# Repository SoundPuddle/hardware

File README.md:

hardware
========

Hardware designs for the SoundPuddle project

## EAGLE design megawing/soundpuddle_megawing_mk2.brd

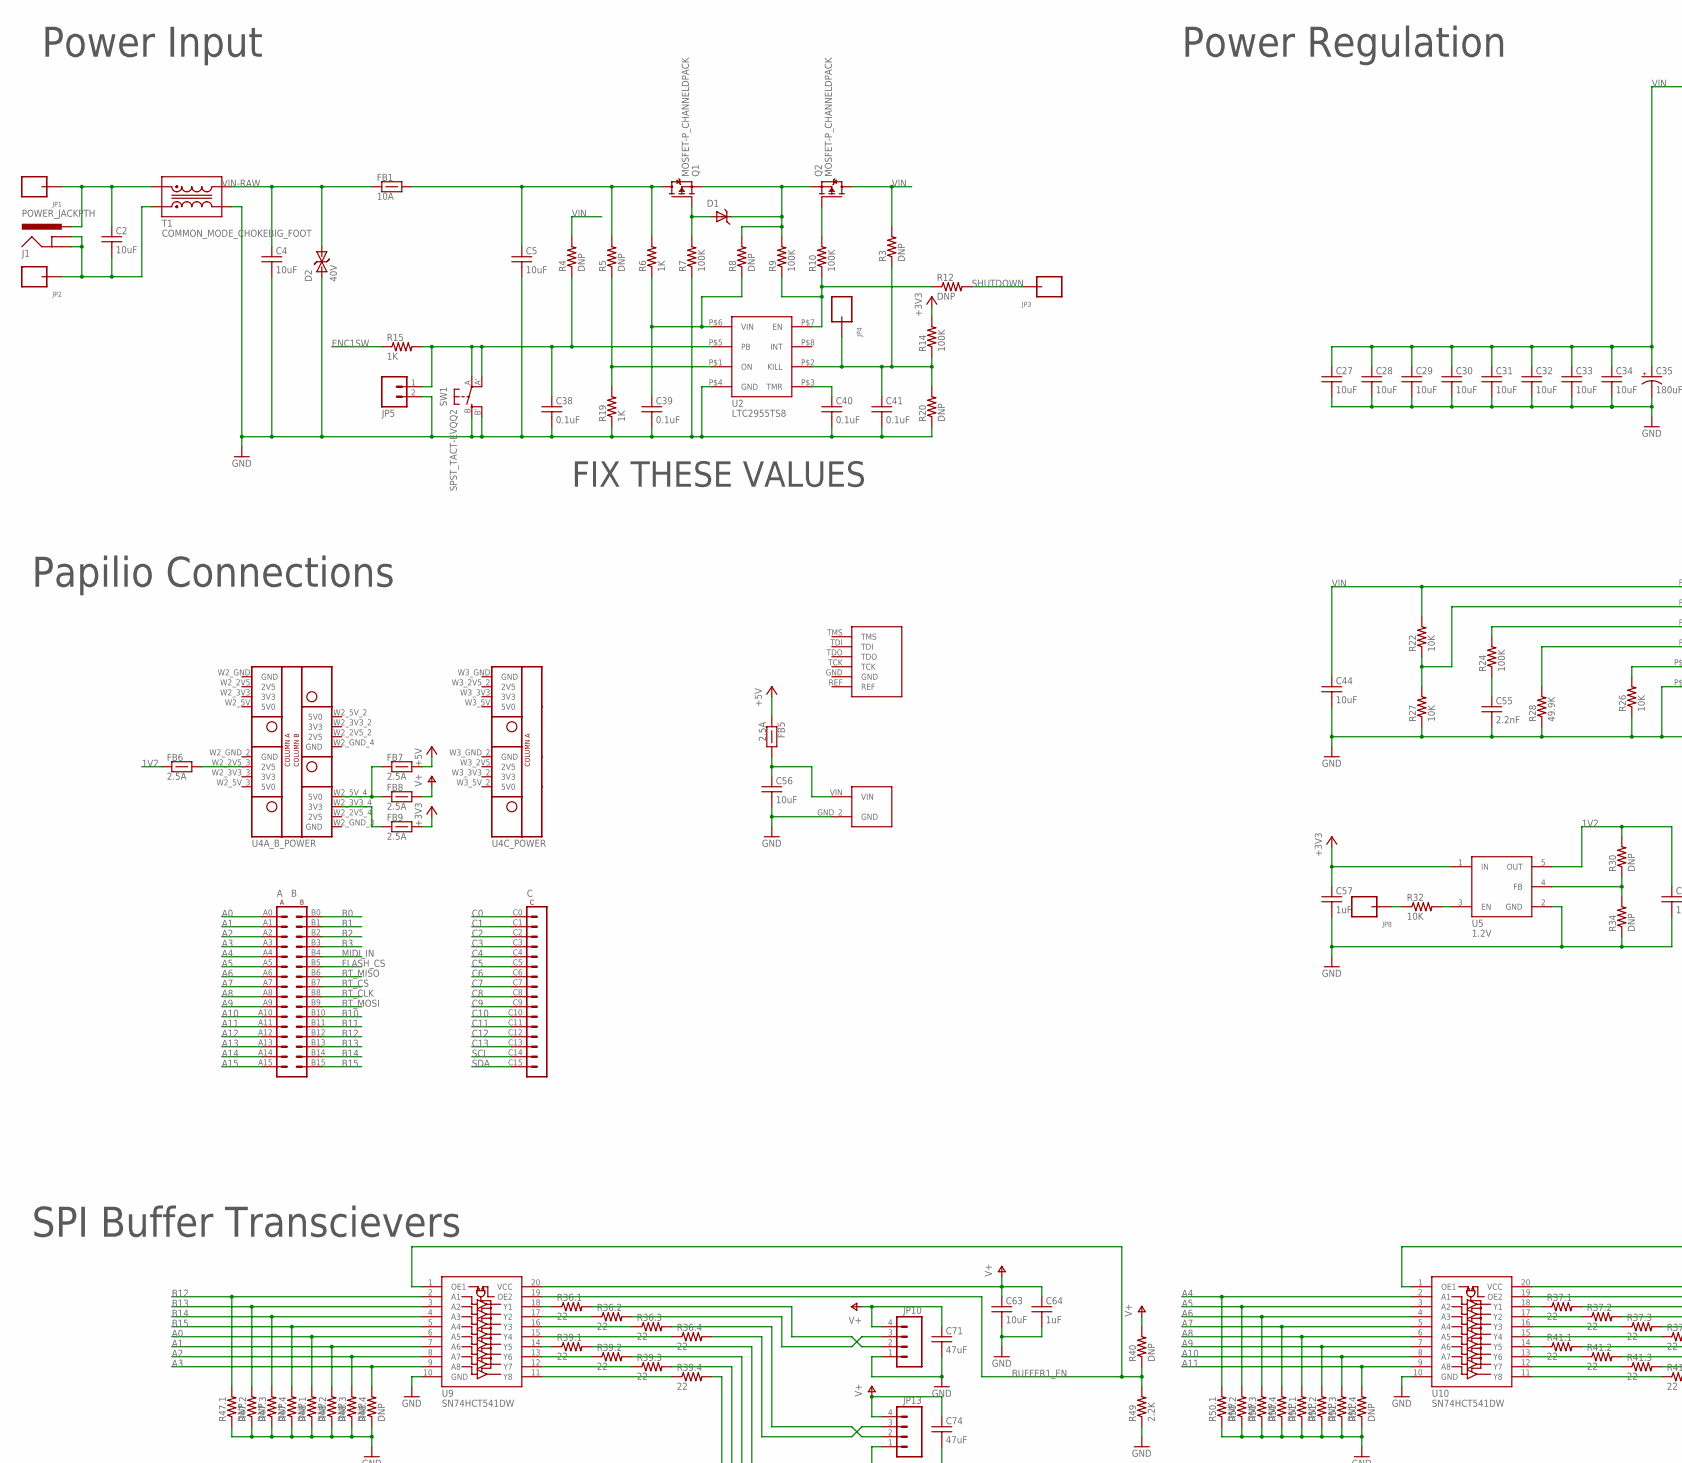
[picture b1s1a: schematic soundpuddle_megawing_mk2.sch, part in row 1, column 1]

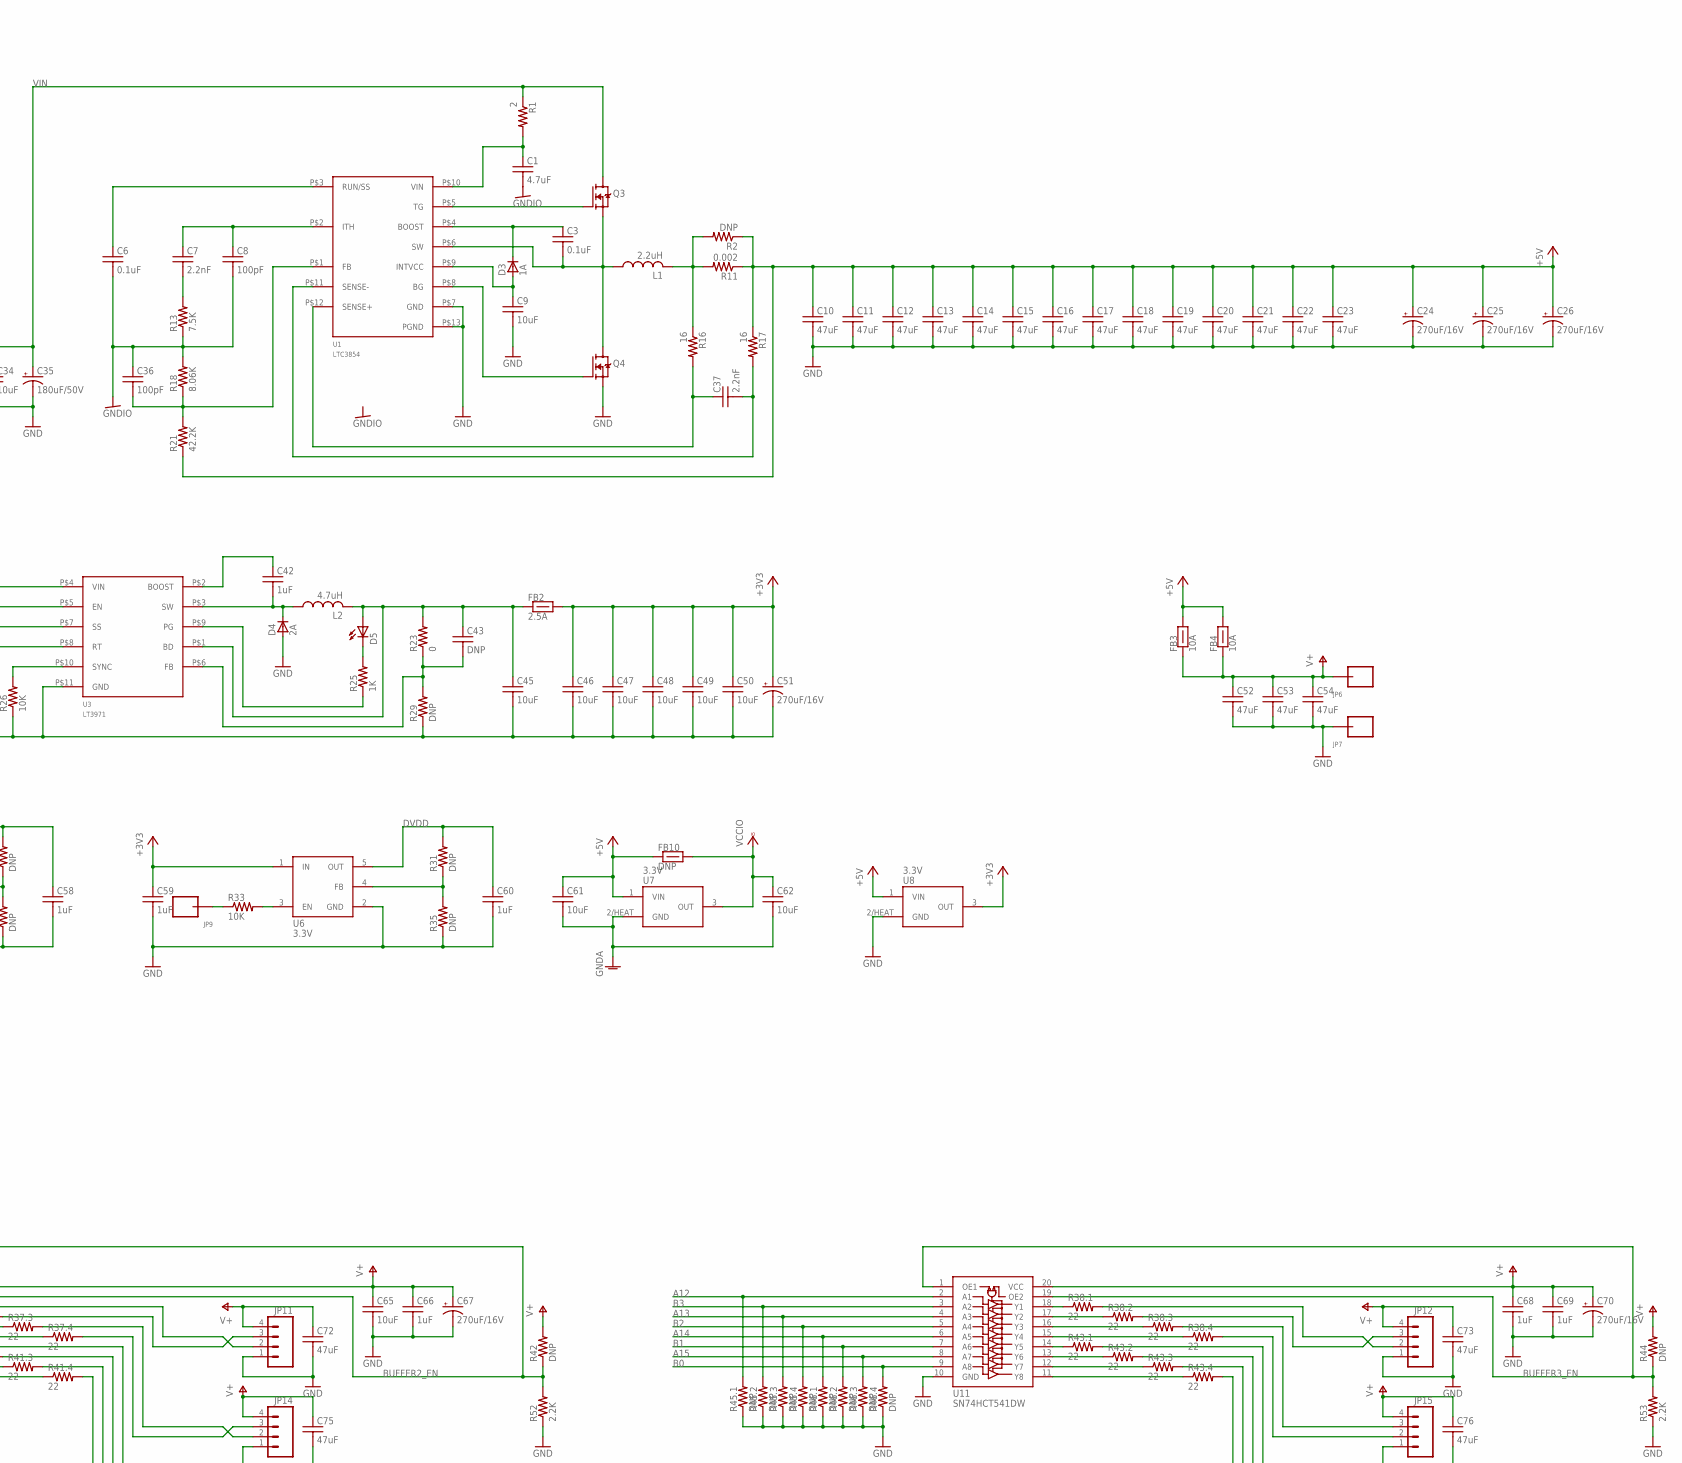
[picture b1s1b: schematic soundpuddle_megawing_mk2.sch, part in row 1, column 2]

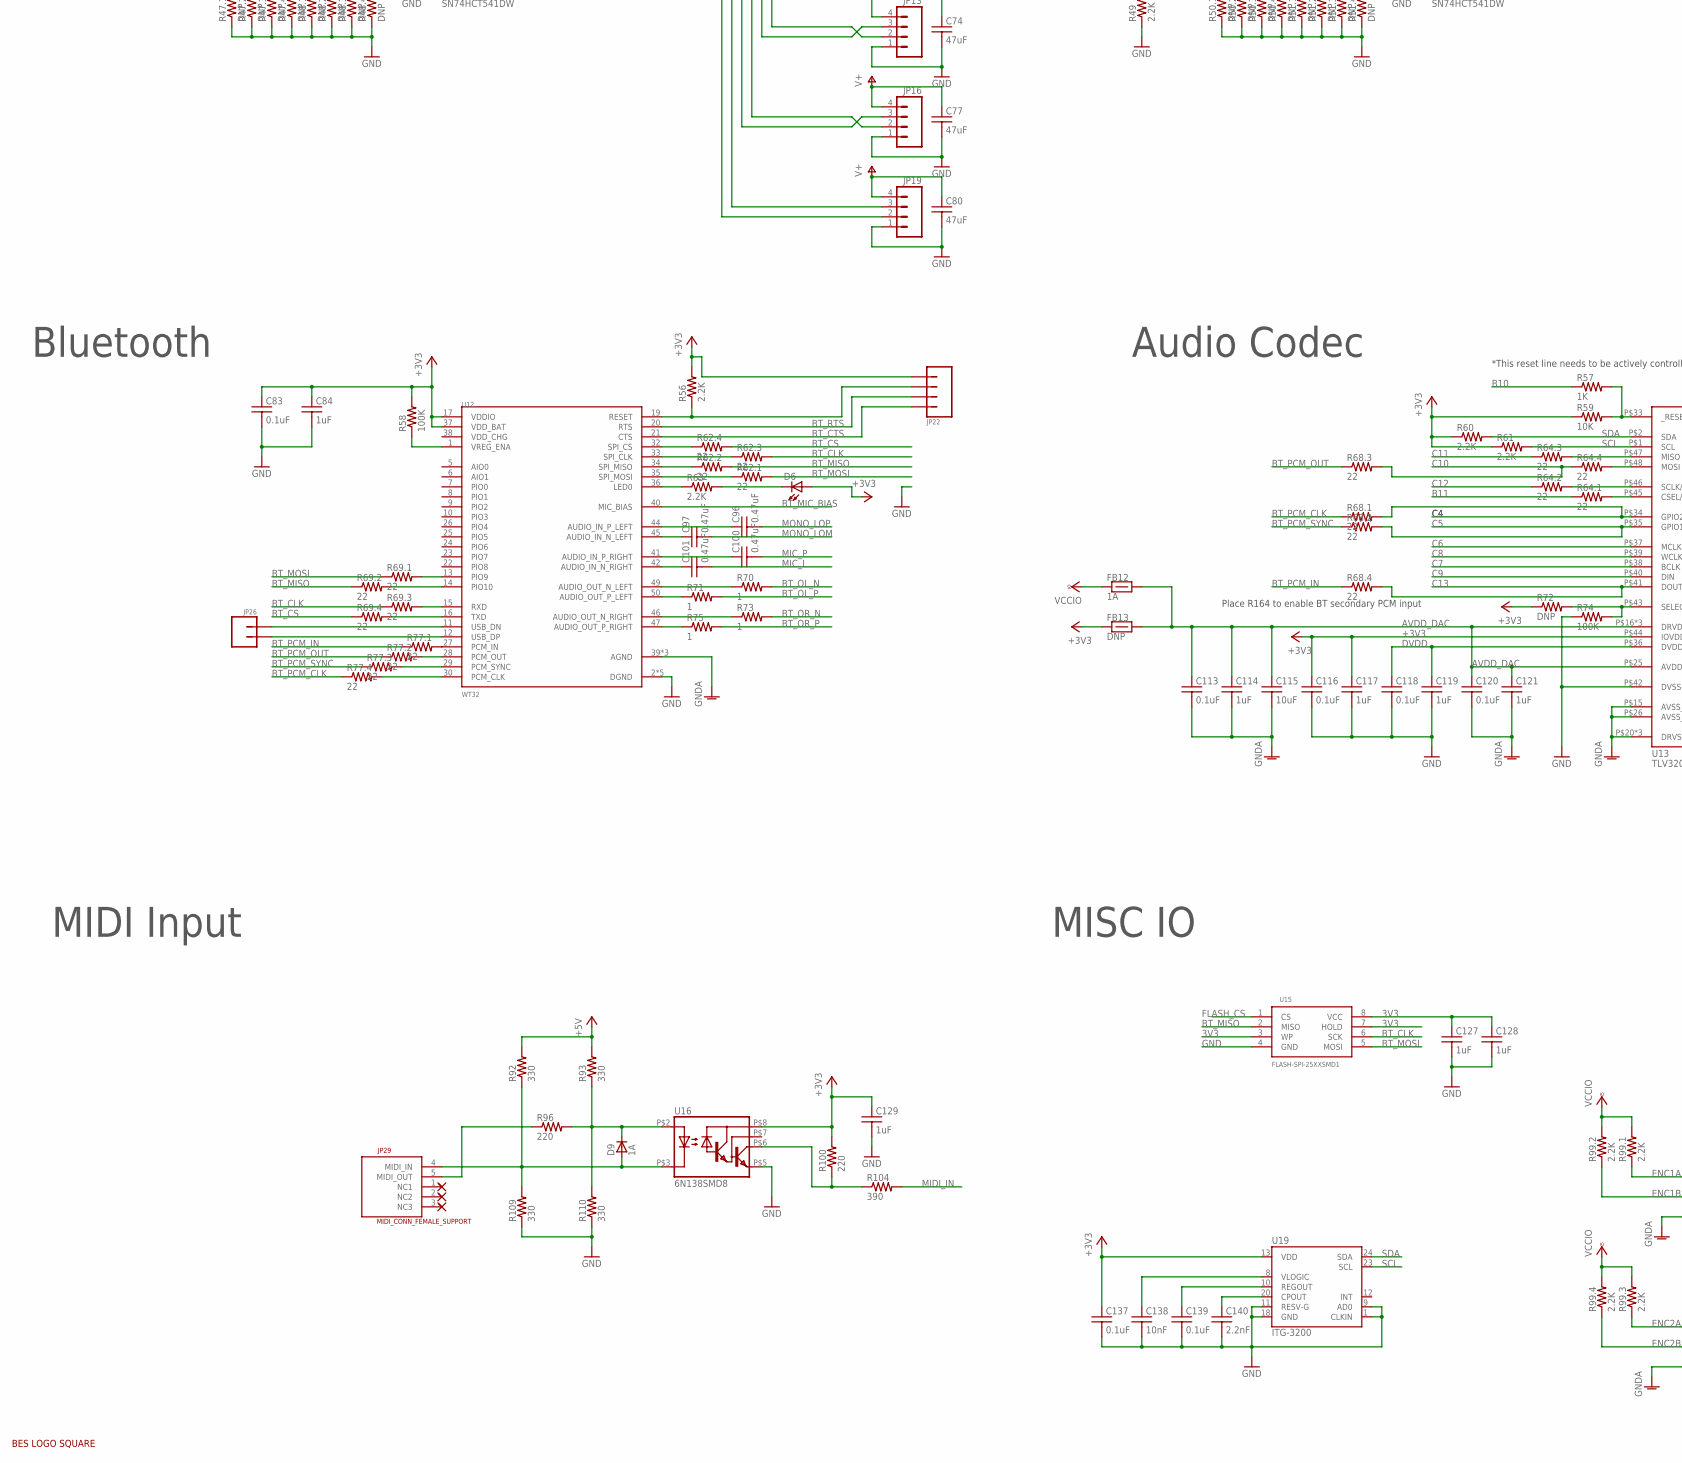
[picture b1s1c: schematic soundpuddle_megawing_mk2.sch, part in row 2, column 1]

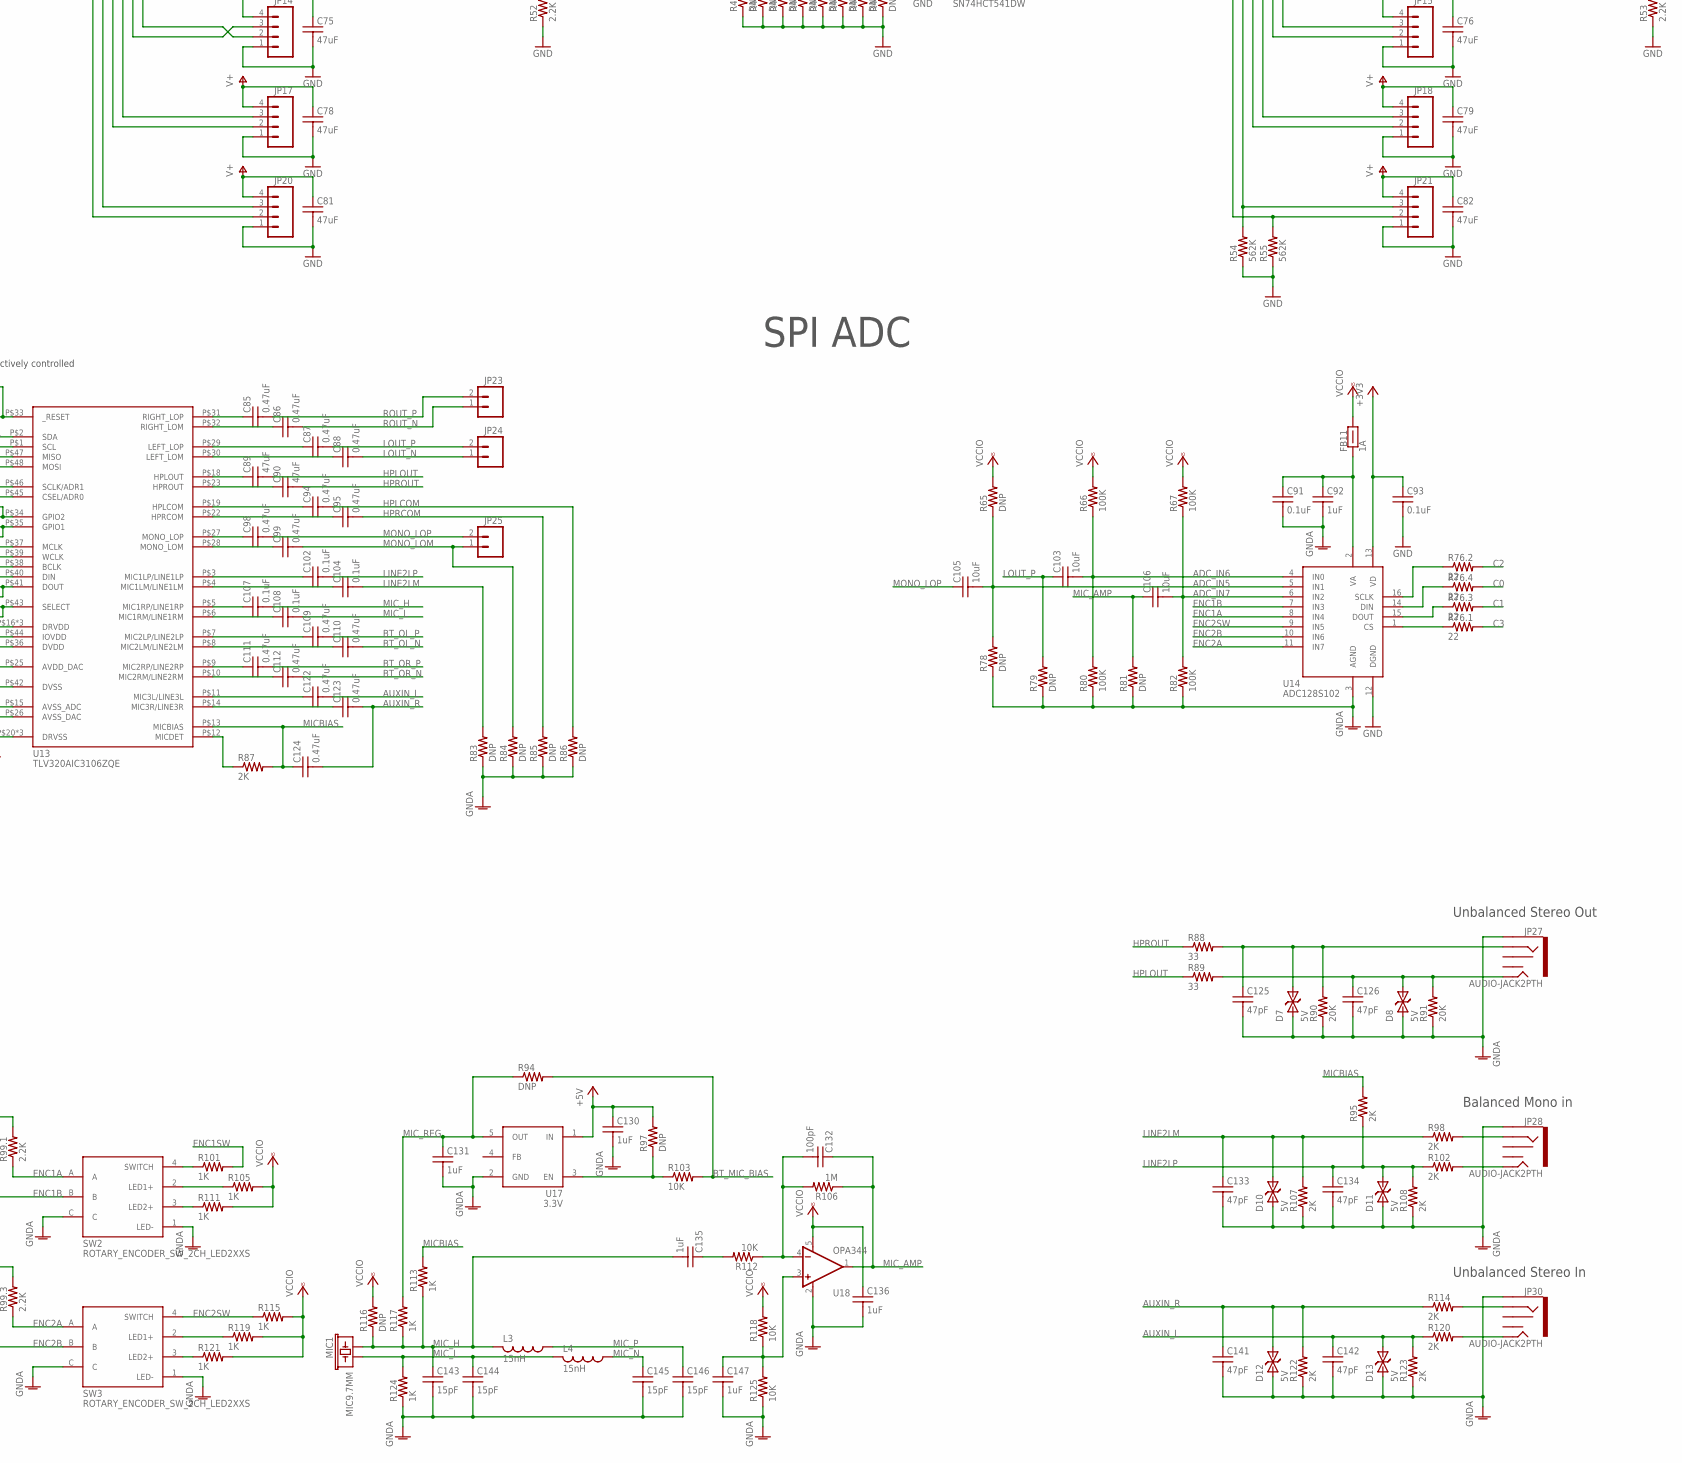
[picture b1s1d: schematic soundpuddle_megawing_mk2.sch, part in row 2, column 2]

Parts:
C1: 4.7uF; 0603
C2, C4, C5, C27, C28, C29, C30, C31, C32, C33, C34, C44, C45, C46, C47, C48, C49, C50, C56, C61, C62: 10uF; 1206
C3, C102, C104: 0.1uF; 0805
C6, C38, C39, C40, C41, C83, C91, C93, C107, C108, C113, C116, C118, C120, C137, C139: 0.1uF; 0603
C7, C37, C55, C140: 2.2nF; 0603
C8, C36, C132: 100pF; 0603
C9, C103, C105, C106, C115: 10uF; 0805
C10, C11, C12, C13, C14, C15, C16, C17, C18, C19, C20, C21, C22, C23, C52, C53, C54, C71, C72, C73, C74, C75, C76, C77, C78, C79, C80, C81, C82, C89, C90: 47uF; 1206
C24, C25, C26, C51, C67, C70: 270uF/16V; CAP_RADIAL_THRUHOLE_8MM_DIA
C35: 180uF/50V; CAP_RADIAL_THRUHOLE_8MM_DIA
C42, C57, C58, C59, C60, C64, C66, C68, C69, C84, C92, C114, C117, C119, C121, C127, C128, C129, C130, C131, C135, C136, C147: 1uF; 0603
C43: DNP; 0603
C63, C65: 10uF; 0603
C85, C86, C87, C88, C94, C95, C96, C97, C98, C99, C100, C101, C109, C110, C111, C112, C122, C123, C124: 0.47uF; 0805
C125, C126, C133, C134, C141, C142: 47pF; 0603
C138: 10nF; 0603
C143, C144, C145, C146: 15pF; 0603
D1: ZENER_SOD-323; SOD-323
D2: 40V; SMB
D3, D9: 1A; SOD-123F
D4: 2A; DIODE_DO-214AC
D5, D6: LED0805; LED_0805
D7, D8, D10, D11, D12, D13: 5V; 0603
FB1, FB3, FB4: 10A; 1612
FB2, FB5, FB6, FB7, FB8, FB9: 2.5A; 0805
FB10, FB13: DNP; 0603
FB11, FB12: 1A; 0603
J1: POWER_JACKPTH; POWER_JACK_PTH
JP1, JP2, JP6, JP7: ANDERSON_POWERPOLEVERTICAL; ANDERSON_25A_VERTICAL_1P
JP3, JP4, JP8, JP9: HEADER-SMALL-1PIN; HEADER-SMALL-1PIN-0.036IN
JP5: M02PTH; 1X02
JP10, JP11, JP12, JP13, JP14, JP15, JP16, JP17, JP18, JP19, JP20, JP21: M04POLAR; MOLEX-1X4
JP22: HEADER-SMALL-4PIN0.1IN; HEADER-SMALL-4PIN-0.036IN
JP23, JP24, JP25: M02POLAR; MOLEX-1X2
JP26: HEADER-SMALL-2PIN0.1IN; HEADER-SMALL-2PIN-0.036IN
JP27, JP28, JP30: AUDIO-JACK2PTH; AUDIO-JACK
JP29: MIDI_CONN_FEMALE_SUPPORT; DIN_5_FEMALE_SUPPORT
L1: 2.2uH; INDUCTOR_HC1
L2: 4.7uH; INDUCTOR_6X6MM
L3, L4: 15nH; 0805
LOGO: LOGO
MIC1: MIC9.7MM; MIC-9.7MM
Q1, Q2: MOSFET-P_CHANNELDPACK; DPACK_1
Q3, Q4: MOSFET_N_CHANNELLFPAK; POWERPAK_SO-8_LFPAK
R1: 2; 0603
R2: DNP; 2512
R3, R4, R5, R8, R12, R20, R29, R30, R31, R34, R35, R40, R42, R44, R65, R72, R78, R79, R81, R83, R84, R85, R86, R94, R97, R116: DNP; 0603
R6, R15, R19, R25, R57, R101, R105, R111, R113, R115, R117, R119, R121, R124: 1K; 0603
R7, R9, R10, R14, R24, R58, R66, R67, R74, R80, R82: 100K; 0603
R11: 0.002; 2512
R13: 7.5K; 0603
R16, R17: 16; 0805
R18: 8.06K; 0603
R21: 42.2K; 0603
R22, R26, R27, R32, R33, R59, R103, R112, R118, R125: 10K; 0603
R23: 0; 0603
R28: 49.9K; 0603
R36, R37, R38, R39, R41, R43, R62, R64, R68, R69, R76, R77: 22; RESISTOR_ARRAY_1206_4CH_CRA06S
R45, R46, R47, R48, R50, R51: DNP; RESISTOR_ARRAY_1206_4CH_CRA06S
R49, R52, R53, R56, R60, R61, R63: 2.2K; 0603
R54, R55: 562K; 0603
R70, R71, R73, R75: 1; 0805
R87, R95, R107, R108, R122, R123: 2K; 0603
R88, R89: 33; 0805
R90, R91: 20K; 0603
R92, R93, R109, R110: 330; 0603
R96, R100: 220; 0603
R98, R102, R114, R120: 2K; 0805
R99: 2.2K; RESISTOR_ARRAY_1206_4CH_CRA06S
R104: 390; 0603
R106: 1M; 0603
SW1: SPST_TACT-EVQQ2; EVQ-Q2
SW2, SW3: ROTARY_ENCODER_SW_2CH_LED2XXS; ROTARY_ENCODER_BOURNS_PEL12D
T1: COMMON_MODE_CHOKEBIG_FOOT; CM-CHOKE_PULSE_BIG-FOOT
U1: LTC3854; MSOP12+1
U2: LTC2955TS8; TSOT-23-8
U3: LT3971; MSOP10+1_LT
U4: PAPILIO_PLUS_MEGAWING; PAPILIO_PLUS
U5: 1.2V; TSOT23
U6, U17: 3.3V; TSOT23
U7, U8: 3.3V; DPACK_1
U9, U10, U11: SN74HCT541DW; SOIC-20_TI_DW
U12: WT32; WT32_BT_MODULE
U13: TLV320AIC3106ZQE; QFN48+1
U14: ADC128S102; TSSOP16
U15: FLASH-SPI-25XXSMD1; SO08-EIAJ
U16: 6N138SMD8; SMD-8
U18: OPA344; SOT23-5
U19: ITG-3200; QFN-24

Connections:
1V2: C58.1, FB6.1, R30.2, U5.5 (OUT)
3V3: C127.1, C128.1, U15.3 (WP), U15.7 (HOLD), U15.8 (VCC)
+3V3: C46.P$1 (1), C47.P$1 (1), C48.P$1 (1), C49.P$1 (1), C50.P$1 (1), C51.P$2 (+), C57.1, C59.1, C83.1, C84.1, C93.1, C116.1, C117.1, C129.1, C137.1, D6.1 (A), FB2.2, FB9.2, FB13.1, JP22.P$4, R14.2, R56.2, R58.2, R59.1, R60.1, R61.1, R72.1, R100.2, U5.1 (IN), U6.1 (IN), U8.3 (OUT), U12.17 (VDDIO), U12.37 (VDD_BAT), U13.P$44 (IOVDD), U14.13 (VD), U16.P$8 (VCC), U19.13 (VDD)
+5V: C10.P$1 (1), C11.P$1 (1), C12.P$1 (1), C13.P$1 (1), C14.P$1 (1), C15.P$1 (1), C16.P$1 (1), C17.P$1 (1), C18.P$1 (1), C19.P$1 (1), C20.P$1 (1), C21.P$1 (1), C22.P$1 (1), C23.P$1 (1), C24.P$2 (+), C25.P$2 (+), C26.P$2 (+), C61.P$1 (1), C130.1, FB3.2, FB4.2, FB5.1, FB7.2, FB10.1, R2.1, R11.1, R17.1, R21.1, R92.2, R93.2, R97.2, U7.1 (VIN), U8.1 (VIN), U17.1 (IN)
A0: R48.P$8 (2), U4.A0, U9.6 (A5)
A1: R48.P$7 (2), U4.A1, U9.7 (A6)
A2: R48.P$6 (2), U4.A2, U9.8 (A7)
A3: R48.P$5 (2), U4.A3, U9.9 (A8)
A4: R50.P$8 (2), U4.A4, U10.2 (A1)
A5: R50.P$7 (2), U4.A5, U10.3 (A2)
A6: R50.P$6 (2), U4.A6, U10.4 (A3)
A7: R50.P$5 (2), U4.A7, U10.5 (A4)
A8: R51.P$8 (2), U4.A8, U10.6 (A5)
A9: R51.P$7 (2), U4.A9, U10.7 (A6)
A10: R51.P$6 (2), U4.A10, U10.8 (A7)
A11: R51.P$5 (2), U4.A11, U10.9 (A8)
A12: R45.P$8 (2), U4.A12, U11.2 (A1)
A13: R45.P$6 (2), U4.A13, U11.4 (A3)
A14: R46.P$8 (2), U4.A14, U11.6 (A5)
A15: R46.P$6 (2), U4.A15, U11.8 (A7)
ADC_IN5: C105.2, R65.1, R78.2, U14.5 (IN1)
ADC_IN6: C103.2, R66.1, R80.2, U14.4 (IN0)
ADC_IN7: C106.2, R67.1, R82.2, U14.6 (IN2)
AUXIN_L: C122.2, C142.1, D13.1 (A), R120.1, R123.2
AUXIN_R: C123.2, C124.2, C141.1, D12.1 (A), R114.1, R122.2
AVDD_DAC: C113.1, C114.1, C115.1, C120.1, C121.1, FB12.2, FB13.2, U13.P$16 (DRVDD), U13.P$17 (DRVDD), U13.P$24 (DRVDD), U13.P$25 (AVDD_DAC)
B0: R46.P$5 (2), U4.B0, U11.9 (A8)
B1: R46.P$7 (2), U4.B1, U11.7 (A6)
B2: R45.P$5 (2), U4.B2, U11.5 (A4)
B3: R45.P$7 (2), U4.B3, U11.3 (A2)
B10: R57.1, U4.B10
B11: R64.P$1 (1), U4.B11
B12: R47.P$8 (2), U4.B12, U9.2 (A1)
B13: R47.P$7 (2), U4.B13, U9.3 (A2)
B14: R47.P$6 (2), U4.B14, U9.4 (A3)
B15: R47.P$5 (2), U4.B15, U9.5 (A4)
BT_CLK: R62.P$6 (2), R69.P$3 (1), U4.B8, U15.6 (SCK)
BT_CS: R62.P$5 (2), R69.P$4 (1), U4.B7
BT_CTS: JP22.P$1, U12.21 (CTS)
BT_MIC_BIAS: R94.2, R103.2, U12.40 (MIC_BIAS)
BT_MISO: R62.P$7 (2), R69.P$2 (1), U4.B6, U15.2 (MISO)
BT_MOSI: R62.P$8 (2), R69.P$1 (1), U4.B9, U15.5 (MOSI)
BT_OL_N: C110.2, R70.2
BT_OL_P: C109.2, R71.2
BT_OR_N: C112.2, R73.2
BT_OR_P: C111.2, R75.2
BT_PCM_CLK: R68.P$1 (1), R77.P$4 (1)
BT_PCM_IN: R68.P$4 (1), R77.P$1 (1)
BT_PCM_OUT: R68.P$3 (1), R77.P$2 (1)
BT_PCM_SYNC: R68.P$2 (1), R77.P$3 (1)
BT_RTS: JP22.P$2, U12.20 (RTS)
BUFFER1_EN: R40.1, R49.2, U9.1 (OE1), U9.19 (OE2)
BUFFER2_EN: R42.1, R52.2, U10.1 (OE1), U10.19 (OE2)
BUFFER3_EN: R44.1, R53.2, U11.1 (OE1), U11.19 (OE2)
C0: R76.P$5 (2), U4.C0
C1: R76.P$6 (2), U4.C1
C2: R76.P$7 (2), U4.C2
C3: R76.P$8 (2), U4.C3
C4: R68.P$8 (2), U4.C4, U13.P$34 (GPIO2)
C5: R68.P$7 (2), U4.C5, U13.P$35 (GPIO1)
C6: U4.C6, U13.P$37 (MCLK)
C7: U4.C7, U13.P$38 (BCLK)
C8: U4.C8, U13.P$39 (WCLK)
C9: U4.C9, U13.P$40 (DIN)
C10: R64.P$4 (1), R68.P$6 (2), U4.C10
C11: R64.P$3 (1), U4.C11
C12: R64.P$2 (1), U4.C12
C13: R68.P$5 (2), U4.C13, U13.P$41 (DOUT)
CH1_CLK: JP10.3, R36.P$7 (2)
CH1_DATA: JP10.2, R36.P$8 (2)
CH2_CLK: JP13.3, R36.P$5 (2)
CH2_DATA: JP13.2, R36.P$6 (2)
CH3_CLK: JP16.3, R39.P$7 (2)
CH3_DATA: JP16.2, R39.P$8 (2)
CH4_CLK: JP19.3, R39.P$6 (2)
CH4_DATA: JP19.2, R39.P$5 (2)
CH5_CLK: JP11.3, R37.P$7 (2)
CH5_DATA: JP11.2, JP14.2, R37.P$6 (2), R37.P$8 (2)
CH6_CLK: JP14.3, R37.P$5 (2)
CH7_CLK: JP17.3, R41.P$8 (2)
CH7_DATA: JP17.2, R41.P$7 (2)
CH8_CLK: JP20.3, R41.P$6 (2)
CH8_DATA: JP20.2, R41.P$5 (2)
CH9_CLK: JP12.3, R38.P$7 (2)
CH9_DATA: JP12.2, R38.P$8 (2)
CH10_CLK: JP15.3, R38.P$6 (2)
CH10_DATA: JP15.2, R38.P$5 (2)
CH11_CLK: JP18.3, R43.P$8 (2)
CH11_DATA: JP18.2, R43.P$7 (2)
CH12_CLK: JP21.3, R43.P$6 (2), R54.2
CH12_DATA: JP21.2, R43.P$5 (2), R55.2
DVDD: C60.1, C118.1, C119.1, R31.2, U6.5 (OUT), U13.P$36 (DVDD)
ENC1A: R99.P$1 (1), SW2.A, U14.8 (IN4)
ENC1B: R99.P$2 (1), SW2.B, U14.7 (IN3)
ENC1SW: R15.1, R101.2
ENC2A: R99.P$3 (1), SW3.A, U14.11 (IN7)
ENC2B: R99.P$4 (1), SW3.B, U14.10 (IN6)
ENC2SW: R115.1, SW3.4 (SWITCH), U14.9 (IN5)
FLASH_CS: U4.B5, U15.1 (CS)
GND: C4.P$2 (2), C5.P$2 (2), C9.2, C10.P$2 (2), C11.P$2 (2), C12.P$2 (2), C13.P$2 (2), C14.P$2 (2), C15.P$2 (2), C16.P$2 (2), C17.P$2 (2), C18.P$2 (2), C19.P$2 (2), C20.P$2 (2), C21.P$2 (2), C22.P$2 (2), C23.P$2 (2), C24.P$1 (-), C25.P$1 (-), C26.P$1 (-), C27.P$2 (2), C28.P$2 (2), C29.P$2 (2), C30.P$2 (2), C31.P$2 (2), C32.P$2 (2), C33.P$2 (2), C34.P$2 (2), C35.P$1 (-), C38.2, C39.2, C40.2, C41.2, C44.P$2 (2), C45.P$2 (2), C46.P$2 (2), C47.P$2 (2), C48.P$2 (2), C49.P$2 (2), C50.P$2 (2), C51.P$1 (-), C52.P$2 (2), C53.P$2 (2), C54.P$2 (2), C55.2, C56.P$2 (2), C57.2, C58.2, C59.2, C60.2, C63.2, C64.2, C65.2, C66.2, C67.P$1 (-), C68.2, C69.2, C70.P$1 (-), C71.P$2 (2), C72.P$2 (2), C73.P$2 (2), C74.P$2 (2), C75.P$2 (2), C76.P$2 (2), C77.P$2 (2), C78.P$2 (2), C79.P$2 (2), C80.P$2 (2), C81.P$2 (2), C82.P$2 (2), C83.2, C84.2, C93.2, C116.2, C117.2, C118.2, C119.2, C127.2, C128.2, C129.2, C137.2, C138.2, C139.2, C140.2, D2.P$2 (C), D4.P$2 (A), JP5.2, JP7.P$1, JP10.1, JP11.1, JP12.1, JP13.1, JP14.1, JP15.1, JP16.1, JP17.1, JP18.1, JP19.1, JP20.1, JP21.1, Q4.1S (S), Q4.2S (S), Q4.3S (S), R7.1, R19.1, R20.1, R26.1, R27.1, R28.1, R29.1, R34.1, R35.1, R45.P$1 (1), R45.P$2 (1), R45.P$3 (1), R45.P$4 (1), R46.P$1 (1), R46.P$2 (1), R46.P$3 (1), R46.P$4 (1), R47.P$1 (1), R47.P$2 (1), R47.P$3 (1), R47.P$4 (1), R48.P$1 (1), R48.P$2 (1), R48.P$3 (1), R48.P$4 (1), R49.1, R50.P$1 (1), R50.P$2 (1), R50.P$3 (1), R50.P$4 (1), R51.P$1 (1), R51.P$2 (1), R51.P$3 (1), R51.P$4 (1), R52.1, R53.1, R54.1, R55.1, R74.1, R109.1, R110.1, SW1.B (S), SW1.B' (S1), T1.P$4 (4), U1.P$7 (GND), U1.P$13 (PGND), U2.P$4 (GND), U3.P$11 (GND), U4.GND_2 (GND), U4.W2_GND (GND), U4.W2_GND_2 (GND), U4.W2_GND_3 (GND), U4.W2_GND_4 (GND), U4.W3_GND (GND), U4.W3_GND_2 (GND), U5.2 (GND), U6.2 (GND), U8.2/HEAT (GND), U9.10 (GND), U10.10 (GND), U11.10 (GND), U12.2 (DGND), U12.3 (DGND), U12.4 (DGND), U12.18 (DGND), U12.31 (DGND), U13.P$42 (DVSS), U14.12 (DGND), U15.4 (GND), U16.P$5 (GND), U19.1 (CLKIN), U19.9 (AD0), U19.11 (RESV-G), U19.18 (GND)
GNDA: C61.P$2 (2), C62.P$2 (2), C91.2, C92.2, C113.2, C114.2, C115.2, C120.2, C121.2, C125.2, C126.2, C130.2, C131.2, C133.2, C134.2, C136.2, C141.2, C142.2, C143.2, C144.2, C145.2, C146.2, C147.2, D7.2 (C), D8.2 (C), D10.2 (C), D11.2 (C), D12.2 (C), D13.2 (C), JP27.SLEEVE, JP28.SLEEVE, JP30.SLEEVE, R78.1, R79.1, R80.1, R81.1, R82.1, R83.1, R84.1, R85.1, R86.1, R90.1, R91.1, R107.1, R108.1, R122.1, R123.1, R124.1, R125.1, SW2.1 (LED-), SW2.C, SW3.1 (LED-), SW3.C, U7.2/HEAT (GND), U12.39 (AGND), U12.43 (AGND), U12.48 (AGND), U13.P$15 (AVSS_ADC), U13.P$20 (DRVSS), U13.P$21 (DRVSS), U13.P$26 (AVSS_DAC), U13.PAD (DRVSS), U14.3 (AGND), U17.2 (GND), U18.2 (V-)
GNDIO: C1.2, C6.2, C8.2, C36.1, R13.1, R18.2
HPLCOM: C94.2, R86.2
HPLOUT: C89.P$2 (2), R89.1
HPRCOM: C95.2, R85.2
HPROUT: C90.P$2 (2), R88.1
LINE2LM: C104.2, C133.1, D10.1 (A), R83.2, R98.1, R107.2
LINE2LP: C102.2, C134.1, D11.1 (A), R95.1, R102.1, R108.2
LOUT_N: C88.2, JP24.1
LOUT_P: C87.2, C103.1, JP24.2, R79.2
MICBIAS: C124.1, R87.2, R95.2, R113.2, U13.P$13 (MICBIAS)
MIC_AMP: C106.1, C132.1, R81.2, R106.1, U18.1 (OUT)
MIC_H: C107.2, C135.2, C143.1, L3.2, MIC1.1, R113.1, R116.1, R117.1
MIC_L: C101.2, C108.2, C144.1, L4.2, MIC1.2, R124.2
MIC_N: C145.1, L4.1
MIC_P: C100.2, C146.1, L3.1
MIC_REG: C131.1, R94.1, R117.2, U17.5 (OUT)
MIDI_IN: R104.2, U4.B4
MONO_LOM: C97.2, C99.2, JP25.1, R84.2
MONO_LOP: C96.2, C98.2, C105.1, JP25.2
unnamed: R76.P$1 (1), U14.1 (CS)
unnamed: R76.P$2 (1), U14.16 (SCLK)
unnamed: R76.P$4 (1), U14.14 (DIN)
unnamed: R76.P$3 (1), U14.15 (DOUT)
unnamed: JP26.P$1, U12.11 (USB_DN)
unnamed: R64.P$5 (2), U13.P$48 (MOSI)
unnamed: C3.2, L1.P$1 (1), Q3.1S (S), Q3.2S (S), Q3.3S (S), Q4.PAD (D), Q4.PAD2 (D), U1.P$6 (SW)
unnamed: R101.1, SW2.4 (SWITCH)
unnamed: R105.1, SW2.2 (LED1+)
unnamed: R111.1, SW2.3 (LED2+)
unnamed: R121.1, SW3.3 (LED2+)
unnamed: R119.1, SW3.2 (LED1+)
unnamed: R30.1, R34.2, U5.4 (FB)
unnamed: JP26.P$2, U12.12 (USB_DP)
unnamed: R62.P$4 (1), U12.32 (SPI_CS)
unnamed: R62.P$3 (1), U12.33 (SPI_CLK)
unnamed: R62.P$2 (1), U12.34 (SPI_MISO)
unnamed: R62.P$1 (1), U12.35 (SPI_MOSI)
unnamed: R32.2, U5.3 (EN)
unnamed: Q3.4G (G), U1.P$5 (TG)
unnamed: C3.1, D3.P$1 (C), U1.P$4 (BOOST)
unnamed: C6.1, U1.P$3 (RUN/SS)
unnamed: C7.2, R13.2
unnamed: C36.2, R18.1, R21.2, U1.P$1 (FB)
unnamed: C7.1, C8.1, U1.P$2 (ITH)
unnamed: Q4.4G (G), U1.P$8 (BG)
unnamed: C9.1, D3.P$2 (A), U1.P$9 (INTVCC)
unnamed: C147.1, R118.1, R125.2, U18.3 (+IN)
unnamed: C135.1, R112.2
unnamed: C56.P$1 (1), FB5.2, U4.VIN
unnamed: C132.2, R106.2, R112.1, U18.4 (-IN)
unnamed: C37.1, R16.2, U1.P$12 (SENSE+)
unnamed: C40.1, U2.P$3 (TMR)
unnamed: C2.P$1 (1), J1.PWR, JP1.P$1, T1.P$1 (1)
unnamed: C37.2, R17.2, U1.P$11 (SENSE-)
unnamed: C2.P$2 (2), J1.GND, J1.GNDBREAK, JP2.P$1, T1.P$2 (3)
unnamed: C4.P$1 (1), D2.P$1 (A), FB1.1, T1.P$3 (2)
unnamed: L1.P$2 (2), R2.2, R11.2, R16.1
unnamed: C1.1, R1.2, U1.P$10 (VIN)
unnamed: C39.1, R6.1, R8.1, U2.P$6 (VIN)
unnamed: JP8.P$1, R32.1
unnamed: Q2.1 (G), R10.2
unnamed: R9.1, R10.1, R12.1, U2.P$7 (EN)
unnamed: D1.A, Q1.1 (G), R7.2
unnamed: C41.1, JP4.P$1, R3.1, R14.1, R20.2, U2.P$2 (KILL)
unnamed: R5.1, R19.2, U2.P$1 (ON)
unnamed: C43.1, C45.P$1 (1), D5.1 (A), FB2.1, L2.P$2 (2), R23.2, U3.P$1 (BD)
unnamed: JP9.P$1, R33.1
unnamed: FB7.1, FB8.1, U4.W2_5V_4 (5V0)
unnamed: FB6.2, U4.W2_2V5_3 (2V5)
unnamed: FB9.1, U4.W2_3V3_4 (3V3)
unnamed: C91.1, C92.1, FB11.1, U14.2 (VA)
unnamed: C140.1, U19.20 (CPOUT)
unnamed: C139.1, U19.10 (REGOUT)
unnamed: C138.1, U19.8 (VLOGIC)
unnamed: C96.1, U12.44 (AUDIO_IN_P_LEFT)
unnamed: C97.1, U12.45 (AUDIO_IN_N_LEFT)
unnamed: R69.P$6 (2), U12.15 (RXD)
unnamed: R69.P$5 (2), U12.16 (TXD)
unnamed: R63.1, U12.36 (LED0)
unnamed: R69.P$8 (2), U12.13 (PIO9)
unnamed: R69.P$7 (2), U12.14 (PIO10)
unnamed: C38.1, JP5.1, R4.1, R15.2, SW1.A, SW1.A' (P1), U2.P$5 (PB)
unnamed: D1.C, Q1.3 (S), Q2.3 (S), R8.2, R9.2
unnamed: R58.1, U12.1 (VREG_ENA)
unnamed: D6.2 (C), R63.2
unnamed: R75.1, U12.47 (AUDIO_OUT_P_RIGHT)
unnamed: R73.1, U12.46 (AUDIO_OUT_N_RIGHT)
unnamed: R71.1, U12.50 (AUDIO_OUT_P_LEFT)
unnamed: R70.1, U12.49 (AUDIO_OUT_N_LEFT)
unnamed: JP22.P$3, R56.1, U12.19 (RESET)
unnamed: C42.2, D4.P$1 (C), L2.P$1 (1), U3.P$3 (SW)
unnamed: C42.1, U3.P$2 (BOOST)
unnamed: R25.1, U3.P$9 (PG)
unnamed: C43.2, R23.1, R29.2, U3.P$6 (FB)
unnamed: R26.2, U3.P$10 (SYNC)
unnamed: R28.2, U3.P$8 (RT)
unnamed: R24.2, U3.P$7 (SS)
unnamed: C55.1, R24.1
unnamed: R22.1, R27.2, U3.P$5 (EN)
unnamed: D5.2 (C), R25.2
unnamed: JP29.5 (MIDI_OUT), R96.1
unnamed: D9.P$1 (C), R93.1, R96.2, R110.2, U16.P$2 (A)
unnamed: D9.P$2 (A), JP29.4 (MIDI_IN), R92.1, R109.2, U16.P$3 (C)
unnamed: R100.1, R104.1, U16.P$6 (VO)
unnamed: R77.P$8 (2), U12.27 (PCM_IN)
unnamed: R77.P$7 (2), U12.28 (PCM_OUT)
unnamed: R77.P$6 (2), U12.29 (PCM_SYNC)
unnamed: R77.P$5 (2), U12.30 (PCM_CLK)
unnamed: R41.P$1 (1), U10.14 (Y5)
unnamed: R37.P$1 (1), U10.18 (Y1)
unnamed: R37.P$2 (1), U10.17 (Y2)
unnamed: R37.P$3 (1), U10.16 (Y3)
unnamed: R37.P$4 (1), U10.15 (Y4)
unnamed: R41.P$2 (1), U10.13 (Y6)
unnamed: R41.P$3 (1), U10.12 (Y7)
unnamed: R41.P$4 (1), U10.11 (Y8)
unnamed: R39.P$1 (1), U9.14 (Y5)
unnamed: R36.P$1 (1), U9.18 (Y1)
unnamed: R36.P$2 (1), U9.17 (Y2)
unnamed: R36.P$3 (1), U9.16 (Y3)
unnamed: R36.P$4 (1), U9.15 (Y4)
unnamed: R39.P$2 (1), U9.13 (Y6)
unnamed: R39.P$3 (1), U9.12 (Y7)
unnamed: R39.P$4 (1), U9.11 (Y8)
unnamed: C100.1, U12.41 (AUDIO_IN_P_RIGHT)
unnamed: C101.1, U12.42 (AUDIO_IN_N_RIGHT)
unnamed: R97.1, R103.1, U17.3 (EN)
unnamed: C85.1, U13.P$31 (RIGHT_LOP)
unnamed: C86.1, U13.P$32 (RIGHT_LOM)
unnamed: C87.1, U13.P$29 (LEFT_LOP)
unnamed: C88.1, U13.P$30 (LEFT_LOM)
unnamed: C89.P$1 (1), U13.P$18 (HPLOUT)
unnamed: C90.P$1 (1), U13.P$23 (HPROUT)
unnamed: C123.1, U13.P$14 (MIC3R/LINE3R)
unnamed: C122.1, U13.P$11 (MIC3L/LINE3L)
unnamed: C109.1, U13.P$7 (MIC2LP/LINE2LP)
unnamed: C110.1, U13.P$8 (MIC2LM/LINE2LM)
unnamed: C111.1, U13.P$9 (MIC2RP/LINE2RP)
unnamed: C112.1, U13.P$10 (MIC2RM/LINE2RM)
unnamed: C94.1, U13.P$19 (HPLCOM)
unnamed: C95.1, U13.P$22 (HPRCOM)
unnamed: C98.1, U13.P$27 (MONO_LOP)
unnamed: C99.1, U13.P$28 (MONO_LOM)
unnamed: C102.1, U13.P$3 (MIC1LP/LINE1LP)
unnamed: R43.P$1 (1), U11.14 (Y5)
unnamed: R38.P$1 (1), U11.18 (Y1)
unnamed: C104.1, U13.P$4 (MIC1LM/LINE1LM)
unnamed: R38.P$2 (1), U11.17 (Y2)
unnamed: R38.P$3 (1), U11.16 (Y3)
unnamed: C107.1, U13.P$5 (MIC1RP/LINE1RP)
unnamed: R38.P$4 (1), U11.15 (Y4)
unnamed: R43.P$2 (1), U11.13 (Y6)
unnamed: R43.P$3 (1), U11.12 (Y7)
unnamed: R43.P$4 (1), U11.11 (Y8)
unnamed: C108.1, U13.P$6 (MIC1RM/LINE1RM)
unnamed: R87.1, U13.P$12 (MICDET)
unnamed: R72.2, R74.2, U13.P$43 (SELECT)
unnamed: R64.P$6 (2), U13.P$47 (MISO)
unnamed: R64.P$7 (2), U13.P$46 (SCLK/ADR1)
unnamed: R64.P$8 (2), U13.P$45 (CSEL/ADR0)
unnamed: R57.2, R59.2, U13.P$33 (_RESET)
unnamed: C125.1, D7.1 (A), JP27.RING, R88.2, R90.2
unnamed: C126.1, D8.1 (A), JP27.TIP, R89.2, R91.2
unnamed: JP30.RING, R114.2
unnamed: JP30.TIP, R120.2
unnamed: JP28.RING, R98.2
unnamed: JP28.TIP, R102.2
unnamed: R31.1, R35.2, U6.4 (FB)
unnamed: R33.2, U6.3 (EN)
ROUT_N: C86.2, JP23.1
ROUT_P: C85.2, JP23.2
SCL: R61.2, U4.C14, U13.P$1 (SCL), U19.23 (SCL)
SDA: R60.2, U4.C15, U13.P$2 (SDA), U19.24 (SDA)
SHUTDOWN: JP3.P$1, R12.2
V+: C52.P$1 (1), C53.P$1 (1), C54.P$1 (1), C63.1, C64.1, C65.1, C66.1, C67.P$2 (+), C68.1, C69.1, C70.P$2 (+), C71.P$1 (1), C72.P$1 (1), C73.P$1 (1), C74.P$1 (1), C75.P$1 (1), C76.P$1 (1), C77.P$1 (1), C78.P$1 (1), C79.P$1 (1), C80.P$1 (1), C81.P$1 (1), C82.P$1 (1), FB3.1, FB4.1, FB8.2, JP6.P$1, JP10.4, JP11.4, JP12.4, JP13.4, JP14.4, JP15.4, JP16.4, JP17.4, JP18.4, JP19.4, JP20.4, JP21.4, R40.2, R42.2, R44.2, U9.20 (VCC), U10.20 (VCC), U11.20 (VCC)
VCCIO: C62.P$1 (1), C136.1, FB10.2, FB11.2, FB12.1, R65.2, R66.2, R67.2, R99.P$5 (2), R99.P$6 (2), R99.P$7 (2), R99.P$8 (2), R105.2, R111.2, R115.2, R116.2, R118.2, R119.2, R121.2, U7.3 (OUT), U18.5 (V+)
VIN: C27.P$1 (1), C28.P$1 (1), C29.P$1 (1), C30.P$1 (1), C31.P$1 (1), C32.P$1 (1), C33.P$1 (1), C34.P$1 (1), C35.P$2 (+), C44.P$1 (1), Q2.2/HEAT (D), Q3.PAD (D), Q3.PAD2 (D), R1.1, R3.2, R4.2, R22.2, U3.P$4 (VIN)
VIN-RAW: C5.P$1 (1), FB1.2, Q1.2/HEAT (D), R5.2, R6.2

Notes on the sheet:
Bluetooth
MIDI Input
FIX THESE VALUES
*This reset line needs to be actively controlled
Place R164 to enable BT secondary PCM input
Unbalanced Stereo Out
Unbalanced Stereo In
Balanced Mono in
Power Input
Power Regulation
SPI Buffer Transcievers
Audio Codec
SPI ADC
Papilio Connections
MISC IO

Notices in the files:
parts and their libraries:
SparkFun: Licensing: CC v3.0 Share-Alike You are welcome to use this library for commercial purposes.
